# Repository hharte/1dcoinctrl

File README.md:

# 1dcoinctrl - Issue 4

## Western Electric 1D/2D Payphone Controller Interface for Asterisk

# WARNING - This project involves potentially lethal High-Voltage!

**_The coin relay in most payphones operates using +/- 130VDC.  This project uses a DC-DC converter to boost 12VDC to 130VDC.  Construction and operation of this circuit should only be performed by people familiar with best practices when operating with high voltage, and using extreme caution._**

I WILL NOT BE HELD LIABLE FOR INJURY OR DEATH RESULTING FROM BUILDING OR USING THIS CIRCUIT.   BUILD AND USE THIS CIRCUIT AT YOUR OWN RISK.

THIS HARDWARE AND SOFTWARE IS PROVIDED "AS IS", WITHOUT WARRANTY OF ANY KIND, EXPRESS OR IMPLIED, INCLUDING BUT NOT LIMITED TO THE WARRANTIES OF MERCHANTABILITY, FITNESS FOR A PARTICULAR PURPOSE AND NONINFRINGEMENT.  IN NO EVENT SHALL HOWARD M. HARTE BE LIABLE FOR ANY CLAIM, DAMAGES OR OTHER LIABILITY, WHETHER IN AN ACTION OF CONTRACT, TORT OR OTHERWISE, ARISING FROM, OUT OF OR IN CONNECTION WITH THE HARDWARE AND SOFTWARE OR THE USE OR OTHER DEALINGS IN THE HARDWARE AND SOFTWARE. 

# Overview

This project aims to emulate a coin line as required by the older "dumb" (ie, non-COCOT) payphones such as the Western Electric 1D "Fortress" series.  This coin line interface connects in between an Asterisk PBX and the payphone.  It provides the coin control functionality as well as the ability to determine whether an initial rate has been deposited, and can also perform the "stuck coin" test.

This project is based on another open-source project (see References below) and has the following goals:

1. Real coin-line signaling, while preserving the payphone earth ground.  This requires both +130VDC (coin collect) and -130VDC (coin refund) as well as +25VDC for the "stuck coin" test and -25VDC for the "initial rate" test.
2. The ability to provide up to four coin lines in a single unit.
3. The ability to count dial pulses from Rotary payphones and provide the digits out-of-band to Asterisk.
4. The ability to be [red-boxed](http://en.wikipedia.org/wiki/Red_box_(phreaking)).

# Pay phone

The payphone is a standard Western Electric 1D phone with a 32B "dumb" chassis.  I also verified that Western Electric 32A and TeleService 4032C chassis work well with this design.

# Coin Line Signaling

All coin line signaling happens with respect to TIP and Ground with the RING open. For the tests, current flowing when voltage is applied indicates that either a coin is present in the hopper, or the initial rate has been deposited.

<table>
  <tr>
   <td>Voltage
   </td>
   <td>Operation
   </td>
  </tr>
  <tr>
   <td>+130VDC
   </td>
   <td>Collect coins.
   </td>
  </tr>
  <tr>
   <td>-130VDC
   </td>
   <td>Refund coins.
   </td>
  </tr>
  <tr>
   <td>+25VDC
   </td>
   <td>Stuck Coin Test
   </td>
  </tr>
  <tr>
   <td>-25VDC
   </td>
   <td>Initial Rate Test
   </td>
  </tr>
</table>

## Controlling the Coin Line Signaling

Control of the coin lines is handled by a PIC18F47Q84 microcontroller.  This microcontroller can sense the line polarity and ON/OFF hook status, the test status, and can control the relays on the controller.

There are three relays that provide common control, and two additional relays per line.

### Common Control Relays

1. **_REFUND_** Relay: When operated will prepare negative voltage to be applied to the TIP when the selected line's COIN_CONTROL relay is operated.  When this relay is operated, either Coin Refund or Initial Rate Test will be performed based on the state of the DISPOSITION relay.

2. **_DISPOSITION_** Relay: When operated will prepare high voltage (either +130VDC or -130VDC, depending on the state of the REFUND relay) to be applied to the TIP when the selected line's COIN_CONTROL relay is operated.  When the DISPOSITION relay is not operated, low voltage (+25VDC or -25VDC) will be applied in order to perform either the initial rate test or the stuck coin test.

3. **_POLE-CHANGER_** Relay: This relay is used to swap the Vout+ and Vout- on the output of the 130VDC DC-DC converter so that both +130VDC and -130VDC are available depending on whether the coin should be collected or refunded.

### Per-Line Relays, one each per coin line:

1. **_HOLD_** Relay: When operated will shunt the TIP and RING towards the CO (Asterisk PBX in our case) with a 120-ohm resistor.  This will keep the line on hold while coin disposition or rate tests are performed.

2. **_COIN_CONTROL_** Relay: When operated, will apply the coin control voltage to the TIP towards the payphone.  When not operated, the TIP and RING from the CO (Asterisk PBX) will be passed through to the payphone.

### Sensors

There are several opto-isolated sensors in the design to provide status to the microcontroller.

1. **_TEST_STATUS_** sensor will go low when current is flowing during a test.  It will be high when current is not flowing.

2. Per-line **_OFF_HOOK_F and OFF_HOOK_R_** sensors (one per line) will go low when current is flowing through the loop to the CO (Asterisk PBX) and can detect forward and reverse polarity.  This current will be flowing either when the payphone is off-hook or when the line is on hold.  Polarity reversal answer supervision, if provided by your telephone line, can be used to determine whether coins should be collected or refunded.  These LEDs will blink rapidly while a rotary payphone is being dialed.

# Microcontroller Firmware

The microcontroller firmware uses the [Arduino](https://www.arduino.cc/) development environment with the [DxCore library](https://github.com/SpenceKonde/DxCore) for ease of development.  The firmware provides a command-line interface via the serial port that uses a command set modeled after the familiar Hayes AT command set.

The command syntax is AT followed by a single character command, and an optional number [1-4] for the coin line to operate on.  If the coin line is omitted, the previously used coin line is assumed.

Commands are as follows:

<table>
  <tr>
   <td><strong><em>Command</em></strong>
   </td>
   <td><strong><em>Description</em></strong>
   </td>
   <td><strong><em>Response</em></strong>
   </td>
  </tr>
  <tr>
   <td>AT
   </td>
   <td>Attention
   </td>
   <td>OK
   </td>
  </tr>
  <tr>
   <td>ATZ
   </td>
   <td>Reset
   </td>
   <td>OK
   </td>
  </tr>
  <tr>
   <td>ATC
   </td>
   <td>Collect coin
   </td>
   <td>OK
   </td>
  </tr>
  <tr>
   <td>ATR
   </td>
   <td>Refund coin
   </td>
   <td>OK
   </td>
  </tr>
  <tr>
   <td>ATI
   </td>
   <td>Initial rate test
   </td>
   <td>0 = Initial rate not deposited
<p>
1 = Initial rate deposited
   </td>
  </tr>
  <tr>
   <td>ATS
   </td>
   <td>Stuck coin test
   </td>
   <td>0 = No coin in escrow.
<p>
1 = Coin in escrow.
   </td>
  </tr>
  <tr>
   <td>ATQ
   </td>
   <td>Query hook state
   </td>
   <td>0 = On hook
<p>
1 = Off hook (normal polarity)
<p>
2 = Off hook (reversed polarity)
   </td>
  </tr>
  <tr>
   <td>ATL
   </td>
   <td>Query selected coin line
   </td>
   <td>1-4
   </td>
  </tr>
  <tr>
   <td>ATH
   </td>
   <td>Hold CO line
   </td>
   <td>OK
   </td>
  </tr>
  <tr>
   <td>ATU
   </td>
   <td>Un-hold CO line
   </td>
   <td>OK
   </td>
  </tr>
  <tr>
   <td>ATD
   </td>
   <td>Dump current controller state
   </td>
   <td>OK
   </td>
  </tr>
  <tr>
   <td>ATE
   </td>
   <td>Stress test 100 refunds (1s apart)
   </td>
   <td>OK
   </td>
  </tr>
  <tr>
   <td>ATT
   </td>
   <td>Coin line simulation
   </td>
   <td>Need hard reset to exit.
   </td>
  </tr>
  <tr>
   <td>ATV
   </td>
   <td>Display firmware version
   </td>
   <td>OK
   </td>
  </tr>
  <tr>
   <td>AT?
   </td>
   <td>Help
   </td>
   <td>Display command help
   </td>
  </tr>
</table>

# Building the Hardware

## Components

The components for this board can be ordered from Digi-Key using [this parts list](https://www.digikey.com/en/mylists/list/BGQKKBOZGS).  The list includes all components and accessories to build the full board supporting all four coin lines.  The user will need to provide their own 12VDC power supply.

There is an [interactive Bill of Materials here](https://html-preview.github.io/?url=https://github.com/hharte/1dcoinctrl/blob/main/hardware/bom/ibom.html).

## Stuffing Options

### Relay Coil Voltage and DC-DC Converters

The schematic/BOM supports either 5V or 12V coil relays.  Alternatively, the board may be built to support a 24VDC input voltage and the user may use 24V coil relays.  In this case, PS1 and PS2 need to change:

<table>
  <tr>
   <td>Power Supply Voltage
   </td>
   <td>Relay Coil Voltage
   </td>
   <td>J8 Setting
   </td>
   <td>PS1 Part
   </td>
   <td>PS2 Part
   </td>
  </tr>
  <tr>
   <td>+12VDC*
   </td>
   <td>12V*
   </td>
   <td>1-2
   </td>
   <td>R12-100B
   </td>
   <td>IA1224S
   </td>
  </tr>
  <tr>
   <td>+12VDC
   </td>
   <td>5V
   </td>
   <td>2-3
   </td>
   <td>R12-100B
   </td>
   <td>IA1224S
   </td>
  </tr>
  <tr>
   <td>+24VDC
   </td>
   <td>5V
   </td>
   <td>2-3
   </td>
   <td>R24-100B
   </td>
   <td>IA2424S
   </td>
  </tr>
  <tr>
   <td>+24VDC
   </td>
   <td>24V
   </td>
   <td>1-2
   </td>
   <td>R24-100B
   </td>
   <td>IA2424S
   </td>
  </tr>
</table>

### Serial Port - RS-232 or 5V TTL-level UART

Communication with the host computer is either via RS-232 or 5V TTL-level UART.

<table>
  <tr>
   <td><strong><em>Reference Designator</em></strong>
   </td>
   <td><strong><em>RS-232</em></strong>
   </td>
   <td><strong><em>TTL UART </em></strong>
   </td>
   <td><strong><em>Notes</em></strong>
   </td>
  </tr>
  <tr>
   <td>U2
   </td>
   <td>✔
   </td>
   <td>
   </td>
   <td>MAX202 or equivalent.
   </td>
  </tr>
  <tr>
   <td>C3,C4,C5,C6,C8
   </td>
   <td>✔
   </td>
   <td>
   </td>
   <td>0.1uF Capacitor
   </td>
  </tr>
  <tr>
   <td>R2
   </td>
   <td>✔
   </td>
   <td>
   </td>
   <td>
   </td>
  </tr>
  <tr>
   <td>C7
   </td>
   <td>✔
   </td>
   <td>
   </td>
   <td>4700pF Capacitor
   </td>
  </tr>
  <tr>
   <td>JP1
   </td>
   <td>✔
   </td>
   <td>
   </td>
   <td>Programming Enable (to program Microcontroller)
<p>
Remove jumper from JP1 when using a standard FTDI 5V TTL UART cable.
   </td>
  </tr>
  <tr>
   <td>JP2, JP3
   </td>
   <td>1-2
   </td>
   <td>2-3
   </td>
   <td>Jumper 1-2 for RS-232 or 2-3 for TTL UART.
   </td>
  </tr>
  <tr>
   <td>J5
   </td>
   <td>✔
   </td>
   <td>✔
   </td>
   <td>6-pin right angle 0.1” male header.
   </td>
  </tr>
</table>

Note: To switch between RS-232 and TTL UART, U2 can be removed from the socket, and the 5V TTL UART cable attached to J5.  When switching back to the RS-232 port, detach the 5V TTL UART cable from J5 and reinstall U2.  In addition to the TTL UART, J5 is also used to program the microcontroller.

### External +/-130VDC Coin Collect / Refund Supply

The board can accommodate an external +/-130VDC supply with the following assembly changes:

<table>
  <tr>
   <td><strong><em>Reference Designator</em></strong>
   </td>
   <td><strong><em>Populate</em></strong>
   </td>
   <td><strong><em>Do Not Populate</em></strong>
   </td>
   <td><strong><em>Notes</em></strong>
   </td>
  </tr>
  <tr>
   <td>PS1
   </td>
   <td>
   </td>
   <td>✔
   </td>
   <td>
   </td>
  </tr>
  <tr>
   <td>C18
   </td>
   <td>
   </td>
   <td>✔
   </td>
   <td>
   </td>
  </tr>
  <tr>
   <td>D2
   </td>
   <td>
   </td>
   <td>✔
   </td>
   <td>
   </td>
  </tr>
  <tr>
   <td>D1
   </td>
   <td>
   </td>
   <td>✔
   </td>
   <td>V_COIN_RELAY (130VDC) Indicator LED.
   </td>
  </tr>
  <tr>
   <td>K1
   </td>
   <td>
   </td>
   <td>✔
   </td>
   <td>Pole Changer Relay
   </td>
  </tr>
  <tr>
   <td>R15
   </td>
   <td>
   </td>
   <td>✔
   </td>
   <td>
   </td>
  </tr>
  <tr>
   <td>R5
   </td>
   <td>
   </td>
   <td>✔
   </td>
   <td>5K Potentiometer
   </td>
  </tr>
  <tr>
   <td>R9
   </td>
   <td>
   </td>
   <td>✔
   </td>
   <td>V_COIN_RELAY (130VDC) Indicator LED current limit.
   </td>
  </tr>
  <tr>
   <td>F2, F3
   </td>
   <td>✔
   </td>
   <td>
   </td>
   <td>125mA Fuse
   </td>
  </tr>
  <tr>
   <td>R10, R11
   </td>
   <td>✔
   </td>
   <td>
   </td>
   <td>+/- 130VDC LED current limiting.
   </td>
  </tr>
  <tr>
   <td>D3, D13
   </td>
   <td>✔
   </td>
   <td>
   </td>
   <td>+/- 130VDC Indicator LEDs
   </td>
  </tr>
</table>

**_Note:_** To switch between external +/-130 VDC supply and the on-board DC-DC converter:

* At minimum, PS1 and K1 should be removed when using the external supply.  If desired, a socket can be made for PS1 by removing several pins from a 24-pin 0.6” wide, machined-pin DIP socket.  A socket can be made for K1 in a similar fashion, using a 16-pin machined-pin DIP socket.
* At minimum, F2, F3 should be removed when using the on-board DC-DC converter.  This is essential for two reasons:
1. Safety: Prevent V_COIN_RELAY (130VDC) from being present on the +/-130VDC terminals of J1.
2. Protection: to ensure that V_COIN_RELAY is not shorted to the +/-130VDC supply during operation.

**_Warning_**

D1, when illuminated, indicates that 130VDC is present on the board.  While this LED is lit, be very careful not to touch the high-voltage section of the board.

D3, D13, when illuminated, indicates that external +/-130VDC is present on the board.  While either of these LEDs are lit, be very careful not to touch the high-voltage section of the board.

### Less Than Four Coin Lines

The controller can be assembled to support fewer than four pay phones.  If only one pay phone is desired, U3 (7406) can be omitted, as well as components associated with lines 2 through 4.

<table>
  <tr>
   <td><strong><em>Coin Line</em></strong>
   </td>
   <td><strong><em>Reference Designator</em></strong>
   </td>
   <td><strong><em>Do Not Populate</em></strong>
   </td>
   <td><strong><em>Notes</em></strong>
   </td>
  </tr>
  <tr>
   <td rowspan="5" >2
   </td>
   <td>D19
   </td>
   <td>✔
   </td>
   <td>Bi-Color LED
   </td>
  </tr>
  <tr>
   <td>D5, D7
   </td>
   <td>✔
   </td>
   <td>1N4148 Switching Diodes
   </td>
  </tr>
  <tr>
   <td>R4, R16, R24
   </td>
   <td>✔
   </td>
   <td>
   </td>
  </tr>
  <tr>
   <td>K3, K6
   </td>
   <td>✔
   </td>
   <td>Hold / Coin Control Relays
   </td>
  </tr>
  <tr>
   <td>U5
   </td>
   <td>✔
   </td>
   <td>Optoisolator
   </td>
  </tr>
  <tr>
   <td rowspan="5" >3
   </td>
   <td>D20
   </td>
   <td>✔
   </td>
   <td>Bi-Color LED
   </td>
  </tr>
  <tr>
   <td>D8, D10
   </td>
   <td>✔
   </td>
   <td>1N4148 Switching Diodes
   </td>
  </tr>
  <tr>
   <td>R3, R18, R26
   </td>
   <td>✔
   </td>
   <td>
   </td>
  </tr>
  <tr>
   <td>K5, K7
   </td>
   <td>✔
   </td>
   <td>Hold / Coin Control Relays
   </td>
  </tr>
  <tr>
   <td>U4
   </td>
   <td>✔
   </td>
   <td>Optoisolator
   </td>
  </tr>
  <tr>
   <td rowspan="5" >4
   </td>
   <td>D21
   </td>
   <td>✔
   </td>
   <td>Bi-Color LED
   </td>
  </tr>
  <tr>
   <td>D9, D11
   </td>
   <td>✔
   </td>
   <td>1N4148 Switching Diodes
   </td>
  </tr>
  <tr>
   <td>R1, R19, R25
   </td>
   <td>✔
   </td>
   <td>
   </td>
  </tr>
  <tr>
   <td>K8, K9
   </td>
   <td>✔
   </td>
   <td>Hold / Coin Control Relays
   </td>
  </tr>
  <tr>
   <td>U1
   </td>
   <td>✔
   </td>
   <td>Optoisolator
   </td>
  </tr>
</table>

## Enclosure

Included in the parts list is a [Hammond 160mm extruded aluminum enclosure](https://www.hammfg.com/files/parts/pdf/1455R1602BK.pdf).  This enclosure includes end caps that can be cut/drilled for the LEDs in the front of the board, as well as the connectors in the rear.  Alternatively, a design for 3D-printed end caps is included in this project.

## Issue 4 PCB

### Microcontroller Replacement

The PIC microcontroller in previous revisions was replaced with an [AVR128DA28](https://www.microchip.com/en-us/product/avr128da28) in the DIP-28 package.  The firmware uses the [Arduino](https://www.arduino.cc/) development environment with the [DxCore library](https://github.com/SpenceKonde/DxCore) for ease of development and programming.

### Other changes between Issue 3 and Issue 4:

* Additional LED connected to microcontroller pin PA7 under firmware control.

Still need to validate:

1. Coin Lines 2, 3, 4.
2. FTDI 5V TTL UART Connection.
3. 

# Connections

## J3, J4 - Lines

The controller supports four CO lines and four coin collectors via two RJ45 connectors.  Each of these connectors is wired according to [T568A](https://en.wikipedia.org/wiki/ANSI/TIA-568).

<table>
  <tr>
   <td><strong><em>Pin</em></strong>
   </td>
   <td><strong><em>T568A Pair</em></strong>
   </td>
   <td><strong><em>J4</em></strong>
<p>
<strong><em>CO Lines</em></strong>
   </td>
   <td><strong><em>J3</em></strong>
<p>
<strong><em>Coin Phones</em></strong>
   </td>
   <td><strong><em>Color</em></strong>
   </td>
  </tr>
  <tr>
   <td>1
   </td>
   <td>3
   </td>
   <td>L3 Tip
   </td>
   <td>L3 Tip
   </td>
   <td>White/Green
   </td>
  </tr>
  <tr>
   <td>2
   </td>
   <td>3
   </td>
   <td>L3 Ring
   </td>
   <td>L3 Ring
   </td>
   <td>Green/White
   </td>
  </tr>
  <tr>
   <td>3
   </td>
   <td>2
   </td>
   <td>L2 Tip
   </td>
   <td>L2 Tip
   </td>
   <td>White/Orange
   </td>
  </tr>
  <tr>
   <td>4
   </td>
   <td>1
   </td>
   <td>L1 Ring
   </td>
   <td>L1 Ring
   </td>
   <td>Blue/White
   </td>
  </tr>
  <tr>
   <td>5
   </td>
   <td>1
   </td>
   <td>L1 Tip
   </td>
   <td>L1 Tip
   </td>
   <td>White/Blue
   </td>
  </tr>
  <tr>
   <td>6
   </td>
   <td>2
   </td>
   <td>L2 Ring
   </td>
   <td>L2 Ring
   </td>
   <td>Orange/White
   </td>
  </tr>
  <tr>
   <td>7
   </td>
   <td>4
   </td>
   <td>L4 Tip
   </td>
   <td>L4 Tip
   </td>
   <td>White/Brown
   </td>
  </tr>
  <tr>
   <td>8
   </td>
   <td>4
   </td>
   <td>L4 Ring
   </td>
   <td>L4 Ring
   </td>
   <td>Brown/White
   </td>
  </tr>
</table>

## J1 - Power

<table>
  <tr>
   <td>Pin
   </td>
   <td>Description
   </td>
  </tr>
  <tr>
   <td>+12VDC
   </td>
   <td>Positive 12V Input.  This must be positive with respect to GROUND.
   </td>
  </tr>
  <tr>
   <td>GROUND
   </td>
   <td>Power Supply Ground (Must be the same as earth ground.)
   </td>
  </tr>
  <tr>
   <td>+130VDC_IN
   </td>
   <td>Coin voltage + (Optional, board assembly option.)
   </td>
  </tr>
  <tr>
   <td>-130VDC_IN
   </td>
   <td>Coin voltage - (Optional, board assembly option.)
   </td>
  </tr>
</table>

## Earth Ground Lug

Coin control and tests are with respect to earth ground.  All payphones must be grounded and bonded for safety as well as to provide a return path for coin collect/refund as well as the initial rate and stuck coin tests.  If the payphone and coin line controller are not grounded, they will not work properly.

## Serial Port

Communication with the host computer running Asterisk is via an RS-232 serial port at J6.  If the user does not wish to use RS-232 levels to communicate with the computer, then the MAX202 IC at U2 should be removed from the socket.  With the MAX202 removed, a [USB to 5V TTL Serial cable](https://www.digikey.com/en/products/detail/ftdi-future-technology-devices-international-ltd/TTL-232R-5V/2003493) connected to J5 (Ground pin on the left when looking at the rear of the controller) can be used to connect the coin controller to a PC via USB.

# Indicators

The controller includes several indicator LEDs.  Most are on the front panel; however, high-voltage warning LEDs are present inside the enclosure.

<table>
  <tr>
   <td><strong><em>Reference Designator</em></strong>
   </td>
   <td><strong><em>Indicates</em></strong>
   </td>
   <td><strong><em>Notes</em></strong>
   </td>
  </tr>
  <tr>
   <td>D15
   </td>
   <td>Power
   </td>
   <td>Illuminates when +5VDC is present, indicating that the coin controller board is powered.
   </td>
  </tr>
  <tr>
   <td>D16
   </td>
   <td>MCU Status
   </td>
   <td>Illuminated under firmware (PA7) control by the on-board microcontroller.
   </td>
  </tr>
  <tr>
   <td>D17
   </td>
   <td>Test Status
   </td>
   <td>Illuminates during the stuck coin test or the initial rate test if the test result is positive: coin is stuck, initial rate is deposited.  This status is input to the microcontroller on PA6.
   </td>
  </tr>
  <tr>
   <td>D18
   </td>
   <td>L1 Status
   </td>
   <td>Line 1 Hook State:
<ul>

<li>Not illuminated: On-hook

<li>Green: Normal Polarity

<li>Red: Reverse Polarity (Answer supervision.)
</li>
</ul>
   </td>
  </tr>
  <tr>
   <td>D19
   </td>
   <td>L2 Status
   </td>
   <td>Line 2 Hook State
   </td>
  </tr>
  <tr>
   <td>D20
   </td>
   <td>L3 Status
   </td>
   <td>Line 1 Hook State
   </td>
  </tr>
  <tr>
   <td>D21
   </td>
   <td>L4 Status
   </td>
   <td>Line 1 Hook State
   </td>
  </tr>
  <tr>
   <td>D1
   </td>
   <td>V_COIN_RELAY
   </td>
   <td>(Internal) 130VDC produced by the on-board DC-DC converter.
   </td>
  </tr>
  <tr>
   <td>D3
   </td>
   <td>+130VDC
   </td>
   <td>(Internal) Indicates +130VDC from the external supply is present.
   </td>
  </tr>
  <tr>
   <td>D13
   </td>
   <td>-130VDC
   </td>
   <td>(Internal) Indicates -130VDC from the external supply is present.
   </td>
  </tr>
</table>

# Asterisk PBX Modifications

Modifications to Asterisk in order to recognize the 1700/2200Hz coin tones is based on [Joshua Stein's project](https://github.com/jcs/payphone) although I modified them to treat the 1700/2200Hz tones as a 5th row/column in the standard [DTMF](http://en.wikipedia.org/wiki/Dual-tone_multi-frequency_signaling) decoding routine in Asterisk's main/dsp.c.

The Asterisk AGI script is not complete, but at present it will prompt for money and can recognize the coin tones.  It will complete the call after 25 cents has been deposited.

## References

* [https://github.com/jcs/payphone](https://github.com/jcs/payphone)
* [Bell System Public Services Crafts' Manual for Station, Network, and Testboard](http://wedophones.com/TheBellSystem/pdf/bsp/coin/PublicServices1.pdf)

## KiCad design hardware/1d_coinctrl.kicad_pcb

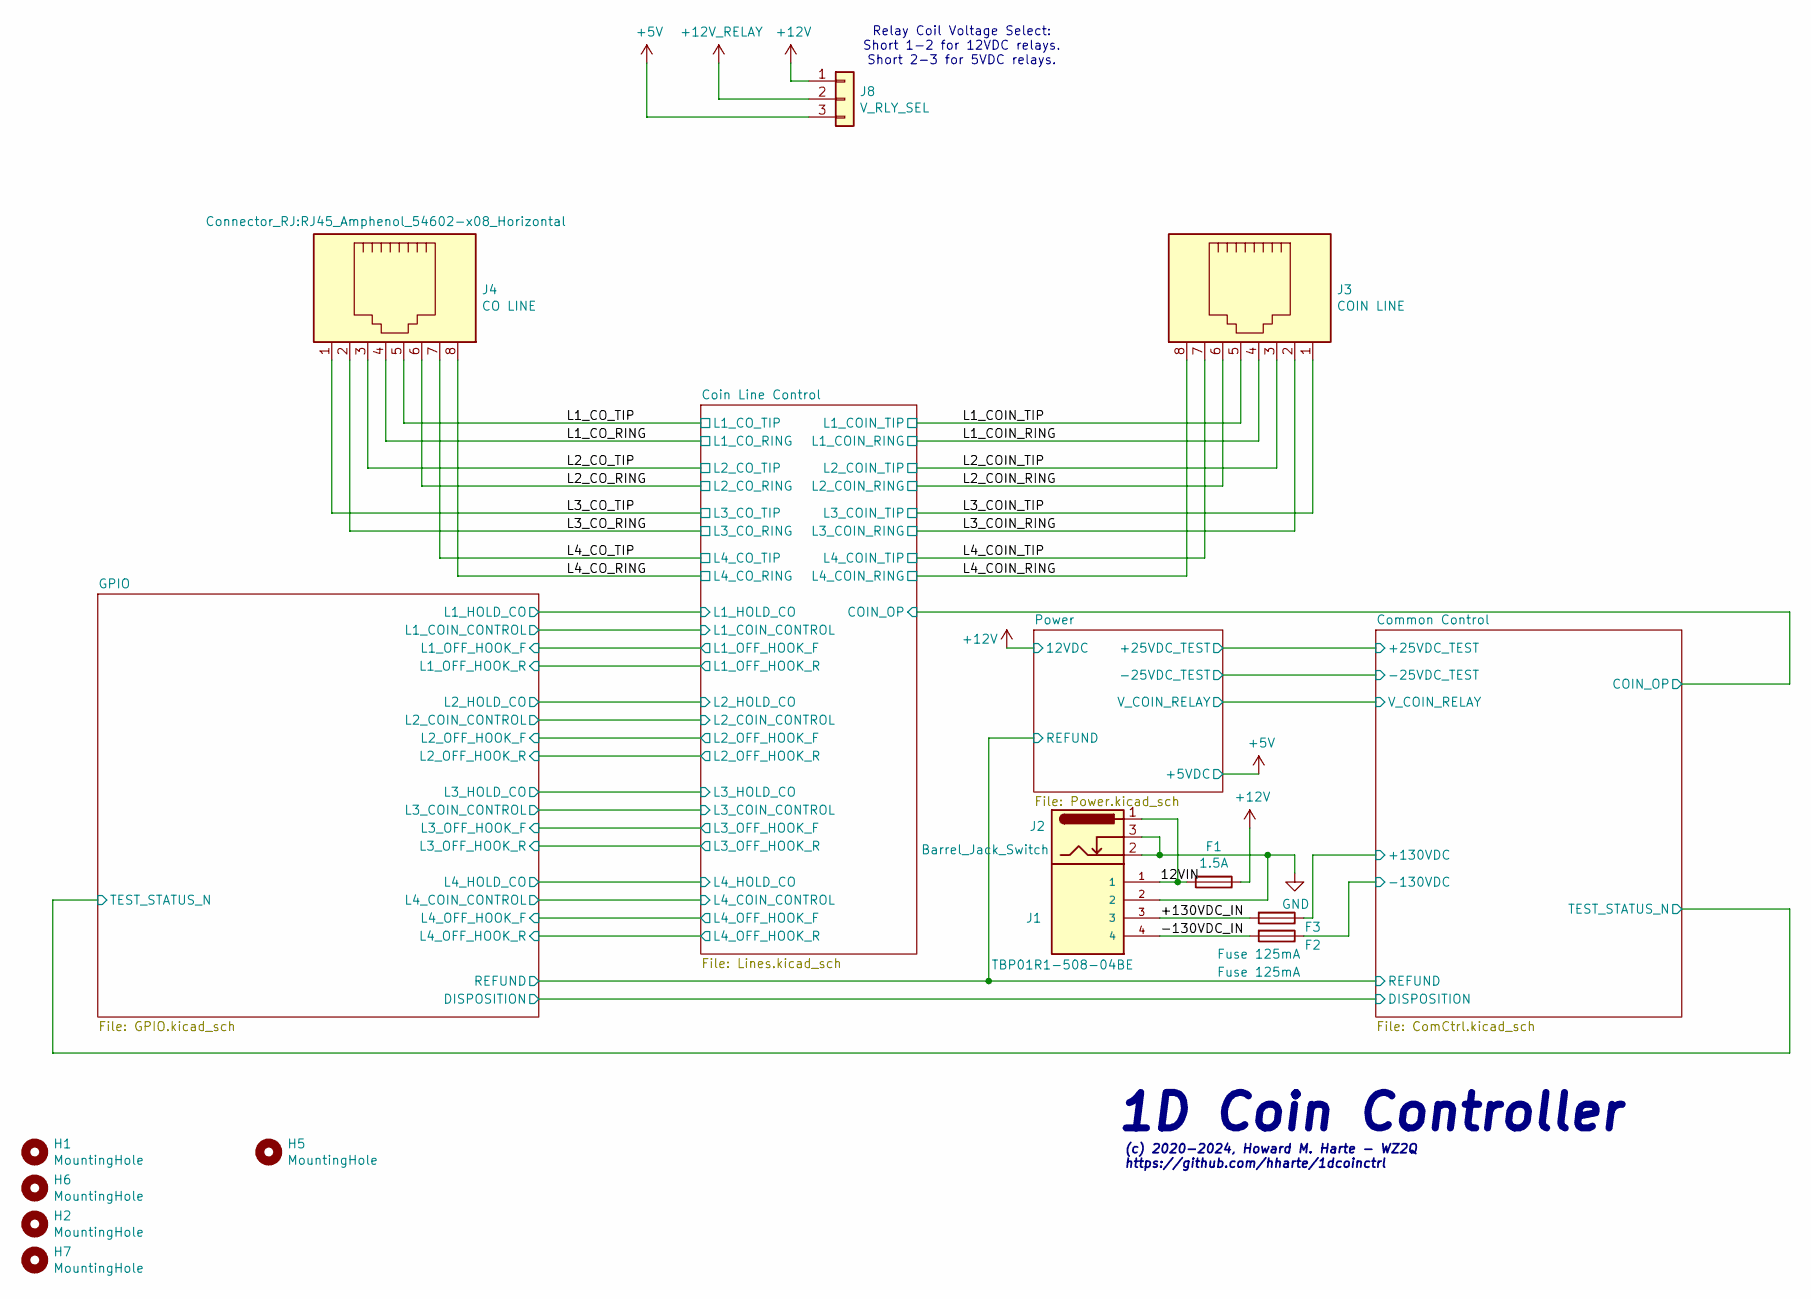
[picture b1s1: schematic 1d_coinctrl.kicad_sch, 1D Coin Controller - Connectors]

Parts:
F1: 1.5A; R_Axial_DIN0207_L6.3mm_D2.5mm_P10.16mm_Horizontal; MPN 025101.5MXL; Digi-Key_PN F2319-ND
F2, F3: Fuse 125mA; R_Axial_DIN0207_L6.3mm_D2.5mm_P10.16mm_Horizontal; MPN 0251.125NAT1L; Digi-Key_PN F10763CT-ND
H1, H2, H5, H6, H7: MountingHole; MountingHole_3.7mm_Pad
J1: TBP01R1-508-04BE; CUI_TBP01R1-508-04BE; MPN TBP01R1-508-04BE; Digi-Key_PN 102-6408-ND
J2: Barrel_Jack_Switch; BarrelJack_Horizontal; MPN RAPC722BK
J3: COIN LINE; RJ45_Amphenol_54602-x08_Horizontal; MPN 54602-908LF; Digi-Key_PN 609-1046-ND
J4: CO LINE; RJ45_Amphenol_54602-x08_Horizontal; MPN 54602-908LF; Digi-Key_PN 609-1046-ND
J8: V_RLY_SEL; PinHeader_1x03_P2.54mm_Vertical

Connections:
+5V: J8.3; also elsewhere on the board
+12V: F1.1, J8.1; also elsewhere on the board
+12V_RELAY: J8.2; also elsewhere on the board
/12VIN: F1.2, J1.1, J2.1
/+130VDC_IN: F3.2, J1.3
/-130VDC_IN: F2.2, J1.4
/Common Control/+130VDC: F3.1; also elsewhere on the board
/Common Control/-130VDC: F2.1; also elsewhere on the board
/L1_COIN_RING: J3.4; also elsewhere on the board
/L1_COIN_TIP: J3.5; also elsewhere on the board
/L1_CO_RING: J4.4; also elsewhere on the board
/L1_CO_TIP: J4.5; also elsewhere on the board
/L2_COIN_RING: J3.6; also elsewhere on the board
/L2_COIN_TIP: J3.3; also elsewhere on the board
/L2_CO_RING: J4.6; also elsewhere on the board
/L2_CO_TIP: J4.3; also elsewhere on the board
/L3_COIN_RING: J3.2; also elsewhere on the board
/L3_COIN_TIP: J3.1; also elsewhere on the board
/L3_CO_RING: J4.2; also elsewhere on the board
/L3_CO_TIP: J4.1; also elsewhere on the board
/L4_COIN_RING: J3.8; also elsewhere on the board
/L4_COIN_TIP: J3.7; also elsewhere on the board
/L4_CO_RING: J4.8; also elsewhere on the board
/L4_CO_TIP: J4.7; also elsewhere on the board
GND: J1.2, J2.2, J2.3; also elsewhere on the board

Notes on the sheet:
(c) 2020-2024, Howard M. Harte - WZ2Q https://github.com/hharte/1dcoinctrl
Relay Coil Voltage Select: Short 1-2 for 12VDC relays. Short 2-3 for 5VDC relays.
1D Coin Controller

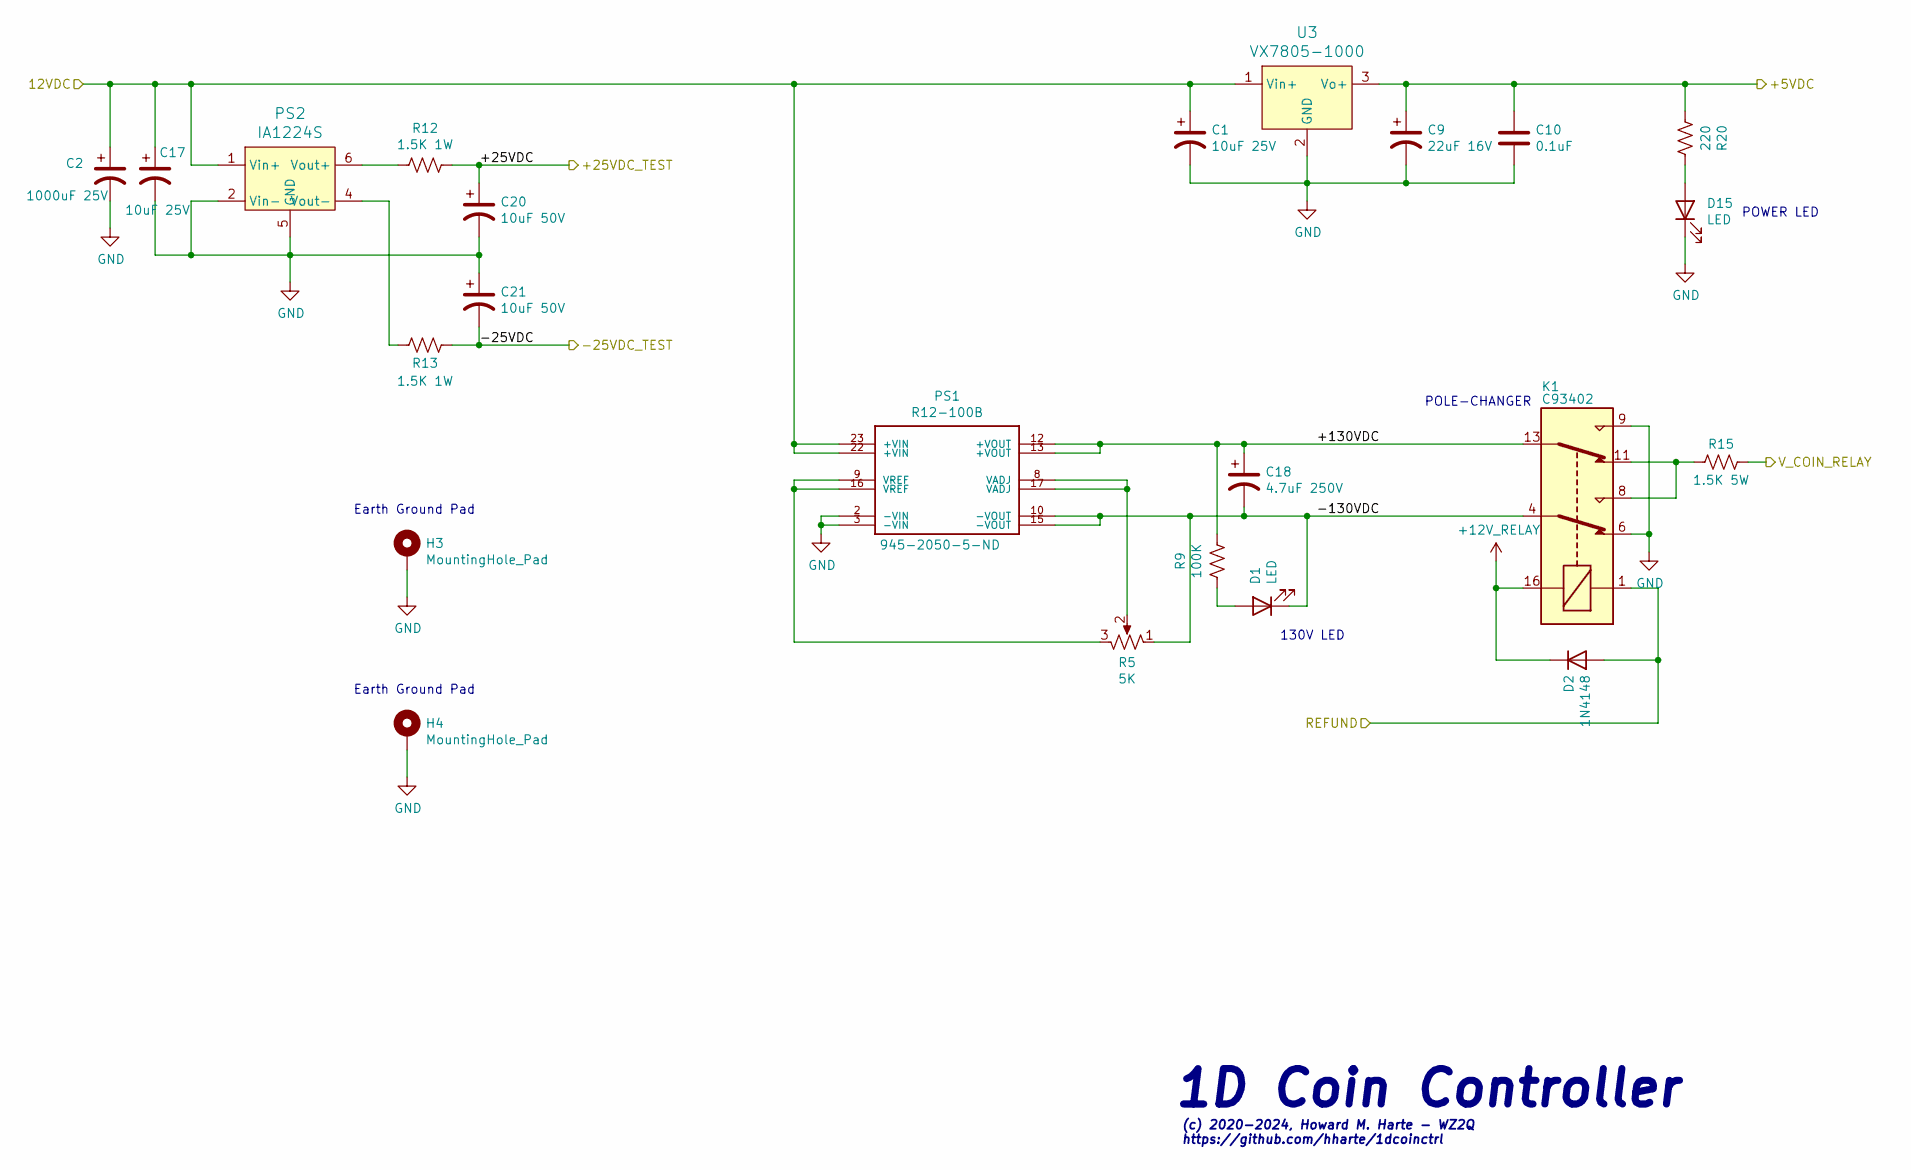
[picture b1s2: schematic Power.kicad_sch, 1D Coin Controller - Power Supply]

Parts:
C1, C17: 10uF 25V; C_Disc_D6.0mm_W4.4mm_P5.00mm; MPN FA26X7R1E106KRU06; Digi-Key_PN 445-180683-1-ND
C2: 1000uF 25V; CP_Radial_D12.5mm_P5.00mm; MPN ECA-1HHG102; Digi-Key_PN P5575-ND
C9: 22uF 16V; C_Disc_D6.0mm_W4.4mm_P5.00mm; MPN FK20X7R1C226MR000; Digi-Key_PN 445-FK20X7R1C226MR000-ND
C10: 0.1uF; C_Disc_D3.0mm_W2.0mm_P2.50mm; MPN K104M15X7RF5TL2; Digi-Key_PN 56-K104M15X7RF5TL2CT-ND
C18: 4.7uF 250V; CP_Radial_D8.0mm_P3.50mm; MPN SEK4R7M250ST; Digi-Key_PN 338-2361-ND
C20, C21: 10uF 50V; CP_Radial_D6.3mm_P2.50mm; MPN ECA-1JM100I; Digi-Key_PN P19534CT-ND
D1, D15: LED; LED_D5.0mm; MPN XLUR12D; Digi-Key_PN 1497-1031-ND
D2: 1N4148; D_DO-35_SOD27_P7.62mm_Horizontal; MPN 1N4148TA; Digi-Key_PN 1N4148TACT-ND
H3, H4: MountingHole_Pad; MountingHole_3.7mm_Pad
K1: C93402; Relay_DPDT_Omron_G5V-2; MPN C93402; Digi-Key_PN PB1125-ND
PS1: R12-100B; CONV_R12-100B; MPN R12-100B; Digi-Key_PN 945-2050-5-ND
PS2: IA1224S; MPN IA1224S; Digi-Key_PN 1470-1364-5-ND
R5: 5K; Potentiometer_Bourns_3266W_Vertical; MPN 64WR5KLF; Digi-Key_PN 987-1067-ND
R9: 100K; R_Axial_DIN0207_L6.3mm_D2.5mm_P7.62mm_Horizontal; MPN CFM12JT100K; Digi-Key_PN S100KHCT-ND
R12, R13: 1.5K 1W; R_Axial_DIN0207_L6.3mm_D2.5mm_P10.16mm_Horizontal; MPN PR01000101501JR500; Digi-Key_PN PPC1.5KW-1CT-ND
R15: 1.5K 5W; R_Axial_Power_L25.0mm_W9.0mm_P30.48mm; MPN EP5WS1K5J; Digi-Key_PN A131371CT-ND
R20: 220; R_Axial_DIN0207_L6.3mm_D2.5mm_P7.62mm_Horizontal; MPN CFM12JT220R; Digi-Key_PN S220HCT-ND
U3: VX7805-1000; MPN VX7805-1000; Digi-Key_PN 102-4253-ND

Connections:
+5V: C9.1, C10.1, R20.2, U3.3 (Vo+); also elsewhere on the board
+12V: C1.1, C2.1, C17.1, PS1.22 (+VIN), PS1.23 (+VIN), PS2.1 (Vin+), U3.1 (Vin+); also elsewhere on the board
+12V_RELAY: D2.1 (K), K1.16; also elsewhere on the board
/Common Control/REFUND: D2.2 (A), K1.1; also elsewhere on the board
/Common Control/V_COIN_RELAY: R15.1; also elsewhere on the board
/Power/+25VDC: C20.1, R12.1; also elsewhere on the board
/Power/+130VDC: C18.1, K1.13, PS1.12 (+VOUT), PS1.13 (+VOUT), R9.1
/Power/-25VDC: C21.2, R13.1; also elsewhere on the board
/Power/-130VDC: C18.2, D1.1 (K), K1.4, PS1.10 (-VOUT), PS1.15 (-VOUT), R5.1
GND: C1.2, C2.2, C9.2, C10.2, C17.2, C20.2, C21.1, D15.1 (K), H3.1, H4.1, K1.6, K1.9, PS1.2 (-VIN), PS1.3 (-VIN), PS2.2 (Vin-), PS2.5 (GND), U3.2 (GND); also elsewhere on the board
unnamed: D1.2 (A), R9.2
unnamed: D15.2 (A), R20.1
unnamed: K1.8, K1.11, R15.2
unnamed: PS1.8 (VADJ), PS1.17 (VADJ), R5.2
unnamed: PS1.9 (VREF), PS1.16 (VREF), R5.3
unnamed: PS2.6 (Vout+), R12.2
unnamed: PS2.4 (Vout-), R13.2

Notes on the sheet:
(c) 2020-2024, Howard M. Harte - WZ2Q https://github.com/hharte/1dcoinctrl
POLE-CHANGER
Earth Ground Pad
1D Coin Controller
130V LED
POWER LED

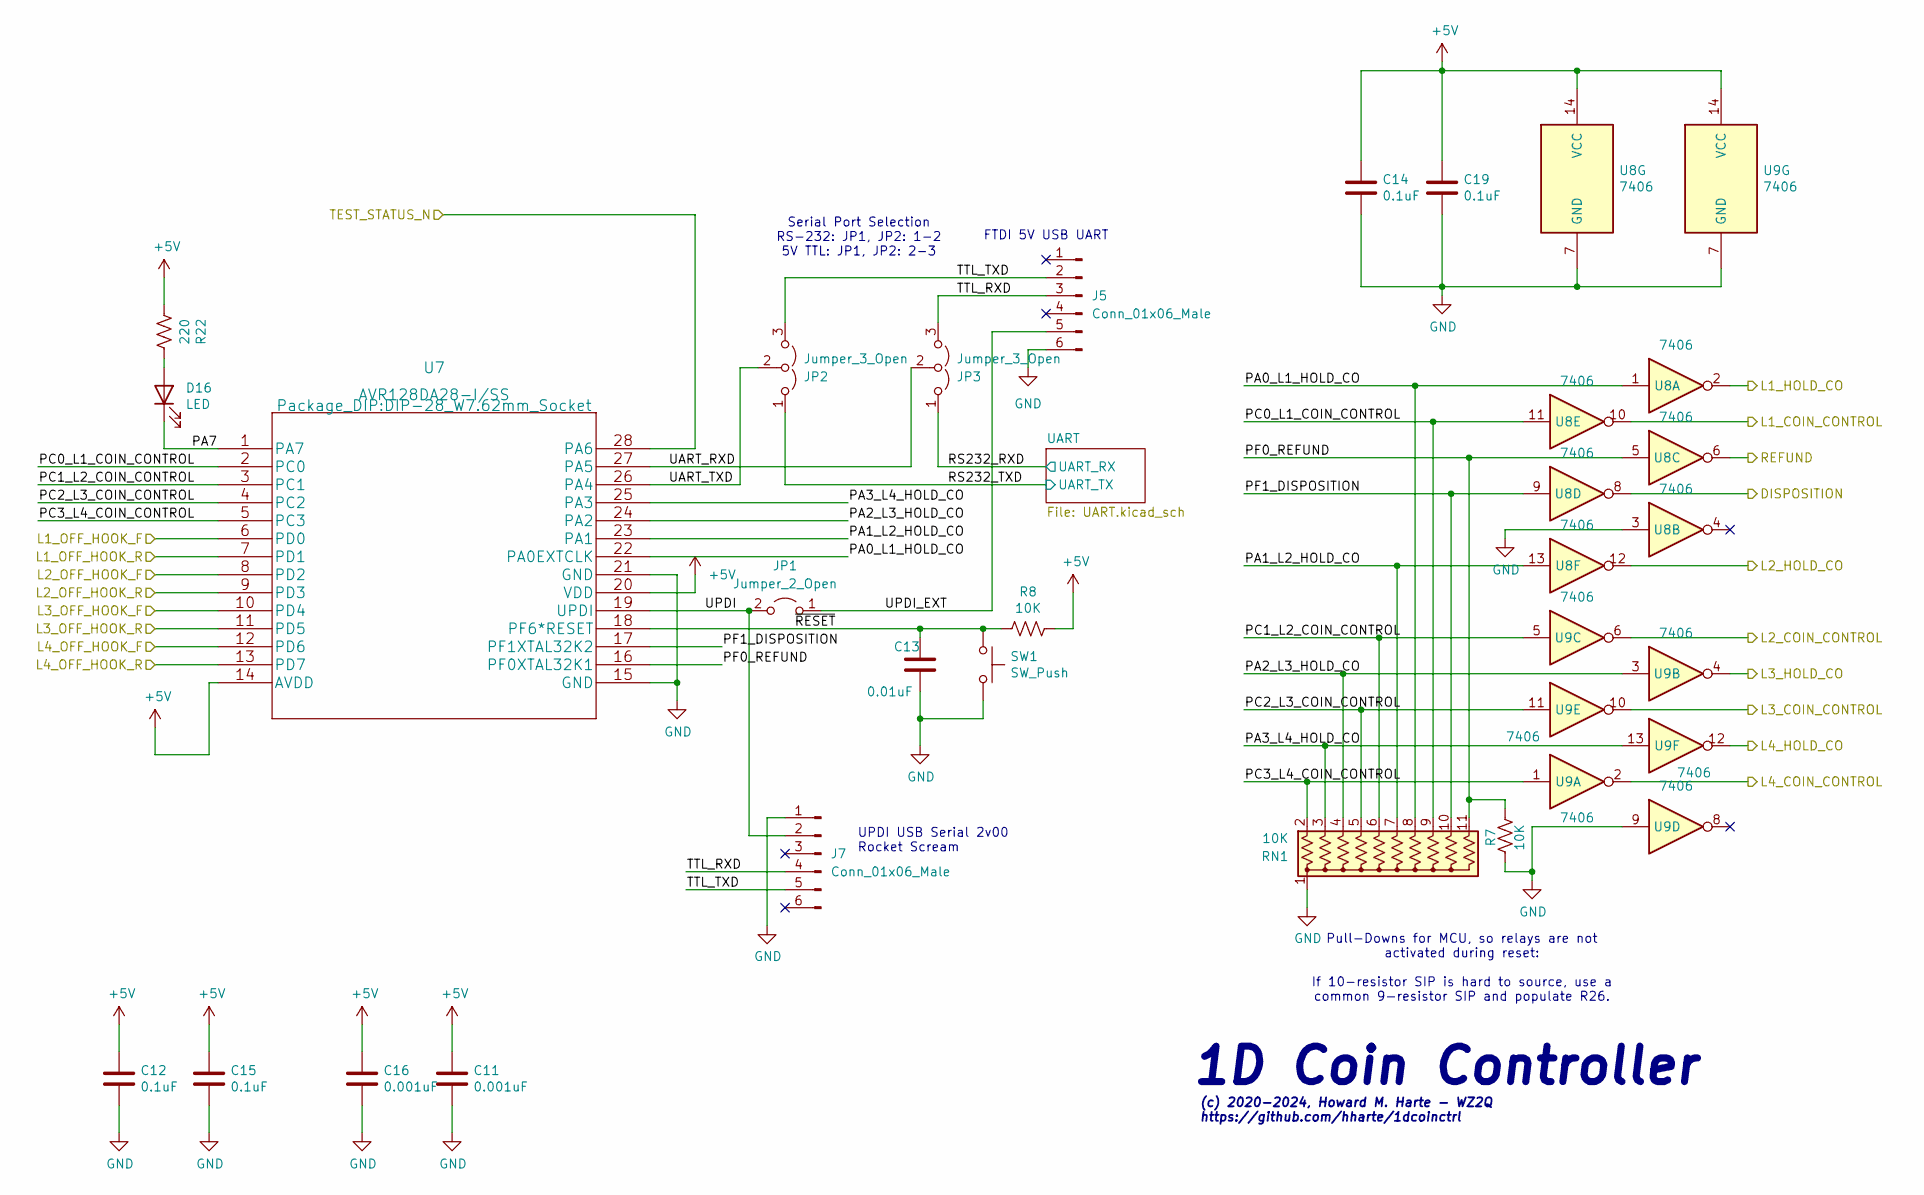
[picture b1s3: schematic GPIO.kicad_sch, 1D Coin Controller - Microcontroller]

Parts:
C11, C16: 0.001uF; C_Disc_D3.0mm_W2.0mm_P2.50mm; MPN K102M15X7RF5UL2; Digi-Key_PN 56-K102M15X7RF5UL2CT-ND
C12, C14, C15, C19: 0.1uF; C_Disc_D3.0mm_W2.0mm_P2.50mm; MPN K104M15X7RF5TL2; Digi-Key_PN 56-K104M15X7RF5TL2CT-ND
C13: 0.01uF; C_Disc_D3.0mm_W1.6mm_P2.50mm; MPN K103K15X7RF5UL2; Digi-Key_PN BC5227CT-ND
D16: LED; LED_D5.0mm; MPN XLUR12D; Digi-Key_PN 1497-1031-ND
J5: Conn_01x06_Male; PinHeader_1x06_P2.54mm_Horizontal; MPN 61300611021; Digi-Key_PN 732-5339-ND
J7: Conn_01x06_Male; PinHeader_1x06_P2.54mm_Vertical; MPN 61300611121; Digi-Key_PN 732-5319-ND
JP1: Jumper_2_Open; PinHeader_1x02_P2.54mm_Vertical
JP2, JP3: Jumper_3_Open; PinHeader_1x03_P2.54mm_Vertical
R7, R8: 10K; R_Axial_DIN0207_L6.3mm_D2.5mm_P7.62mm_Horizontal; MPN CFM12JT10K0; Digi-Key_PN S10KHCT-ND
R22: 220; R_Axial_DIN0207_L6.3mm_D2.5mm_P7.62mm_Horizontal; MPN CFM12JT220R; Digi-Key_PN S220HCT-ND
RN1: 10K; R_Array_SIP11; MPN 4611X-101-103LF; Digi-Key_PN 4611X-101-103LF-ND
SW1: SW_Push; SW_PUSH_6mm; MPN 1301.9302; Digi-Key_PN 486-3458-ND
U7: AVR128DA28-I/SS; DIP-28_W7.62mm_Socket; MPN AVR128DA28-E/SP; Digi-Key_PN 150-AVR128DA28-E/SP-ND
U8, U9: 7406; DIP-14_W7.62mm; MPN SN7406N; Digi-Key_PN 296-1435-5-ND

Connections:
+5V: C11.1, C12.1, C14.1, C15.1, C16.1, C19.1, R8.1, R22.2, U7.14 (AVDD), U7.20 (VDD), U8.14 (VCC), U9.14 (VCC); also elsewhere on the board
/Coin Line Control/L1_COIN_CONTROL: U8.10; also elsewhere on the board
/Coin Line Control/L1_HOLD_CO: U8.2; also elsewhere on the board
/Coin Line Control/L1_OFF_HOOK_F: U7.6 (PD0); also elsewhere on the board
/Coin Line Control/L1_OFF_HOOK_R: U7.7 (PD1); also elsewhere on the board
/Coin Line Control/L2_COIN_CONTROL: U9.6; also elsewhere on the board
/Coin Line Control/L2_HOLD_CO: U8.12; also elsewhere on the board
/Coin Line Control/L2_OFF_HOOK_F: U7.8 (PD2); also elsewhere on the board
/Coin Line Control/L2_OFF_HOOK_R: U7.9 (PD3); also elsewhere on the board
/Coin Line Control/L3_COIN_CONTROL: U9.10; also elsewhere on the board
/Coin Line Control/L3_HOLD_CO: U9.4; also elsewhere on the board
/Coin Line Control/L3_OFF_HOOK_F: U7.10 (PD4); also elsewhere on the board
/Coin Line Control/L3_OFF_HOOK_R: U7.11 (PD5); also elsewhere on the board
/Coin Line Control/L4_COIN_CONTROL: U9.2; also elsewhere on the board
/Coin Line Control/L4_HOLD_CO: U9.12; also elsewhere on the board
/Coin Line Control/L4_OFF_HOOK_F: U7.12 (PD6); also elsewhere on the board
/Coin Line Control/L4_OFF_HOOK_R: U7.13 (PD7); also elsewhere on the board
/Common Control/DISPOSITION: U8.8; also elsewhere on the board
/Common Control/REFUND: U8.6; also elsewhere on the board
/Common Control/TEST_STATUS_N: U7.28 (PA6); also elsewhere on the board
/GPIO/PA0_L1_HOLD_CO: RN1.8 (R7), U7.22 (PA0EXTCLK), U8.1
/GPIO/PA1_L2_HOLD_CO: RN1.7 (R6), U7.23 (PA1), U8.13
/GPIO/PA2_L3_HOLD_CO: RN1.4 (R3), U7.24 (PA2), U9.3
/GPIO/PA3_L4_HOLD_CO: RN1.3 (R2), U7.25 (PA3), U9.13
/GPIO/PA7: D16.1 (K), U7.1 (PA7)
/GPIO/PC0_L1_COIN_CONTROL: RN1.9 (R8), U7.2 (PC0), U8.11
/GPIO/PC1_L2_COIN_CONTROL: RN1.6 (R5), U7.3 (PC1), U9.5
/GPIO/PC2_L3_COIN_CONTROL: RN1.5 (R4), U7.4 (PC2), U9.11
/GPIO/PC3_L4_COIN_CONTROL: RN1.2 (R1), U7.5 (PC3), U9.1
/GPIO/PF0_REFUND: R7.1, RN1.11 (R10), U7.16 (PF0XTAL32K1), U8.5
/GPIO/PF1_DISPOSITION: RN1.10 (R9), U7.17 (PF1XTAL32K2), U8.9
/GPIO/RS232_RXD: JP3.1 (A); also elsewhere on the board
/GPIO/RS232_TXD: JP2.1 (A); also elsewhere on the board
/GPIO/TTL_RXD: J5.3, J7.4, JP3.3 (B)
/GPIO/TTL_TXD: J5.2, J7.5, JP2.3 (B)
/GPIO/UART_RXD: JP3.2 (C), U7.27 (PA5)
/GPIO/UART_TXD: JP2.2 (C), U7.26 (PA4)
/GPIO/UPDI: J7.2, JP1.2 (B), U7.19 (UPDI)
/GPIO/UPDI_EXT: J5.5, JP1.1 (A)
/GPIO/~RESET: C13.1, R8.2, SW1.1, U7.18 (PF6*RESET)
GND: C11.2, C12.2, C13.2, C14.2, C15.2, C16.2, C19.2, J5.6, J7.1, R7.2, RN1.1 (common), SW1.2, U7.15 (GND), U7.21 (GND), U8.3, U8.7 (GND), U9.7 (GND), U9.9; also elsewhere on the board
unnamed: D16.2 (A), R22.1

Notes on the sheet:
UPDI USB Serial 2v00 Rocket Scream
Serial Port Selection RS-232: JP1, JP2: 1-2 5V TTL: JP1, JP2: 2-3
1D Coin Controller
(c) 2020-2024, Howard M. Harte - WZ2Q https://github.com/hharte/1dcoinctrl
FTDI 5V USB UART
Pull-Downs for MCU, so relays are not activated during reset: If 10-resistor SIP is hard to source, use a common 9-resistor SIP and populate R26.

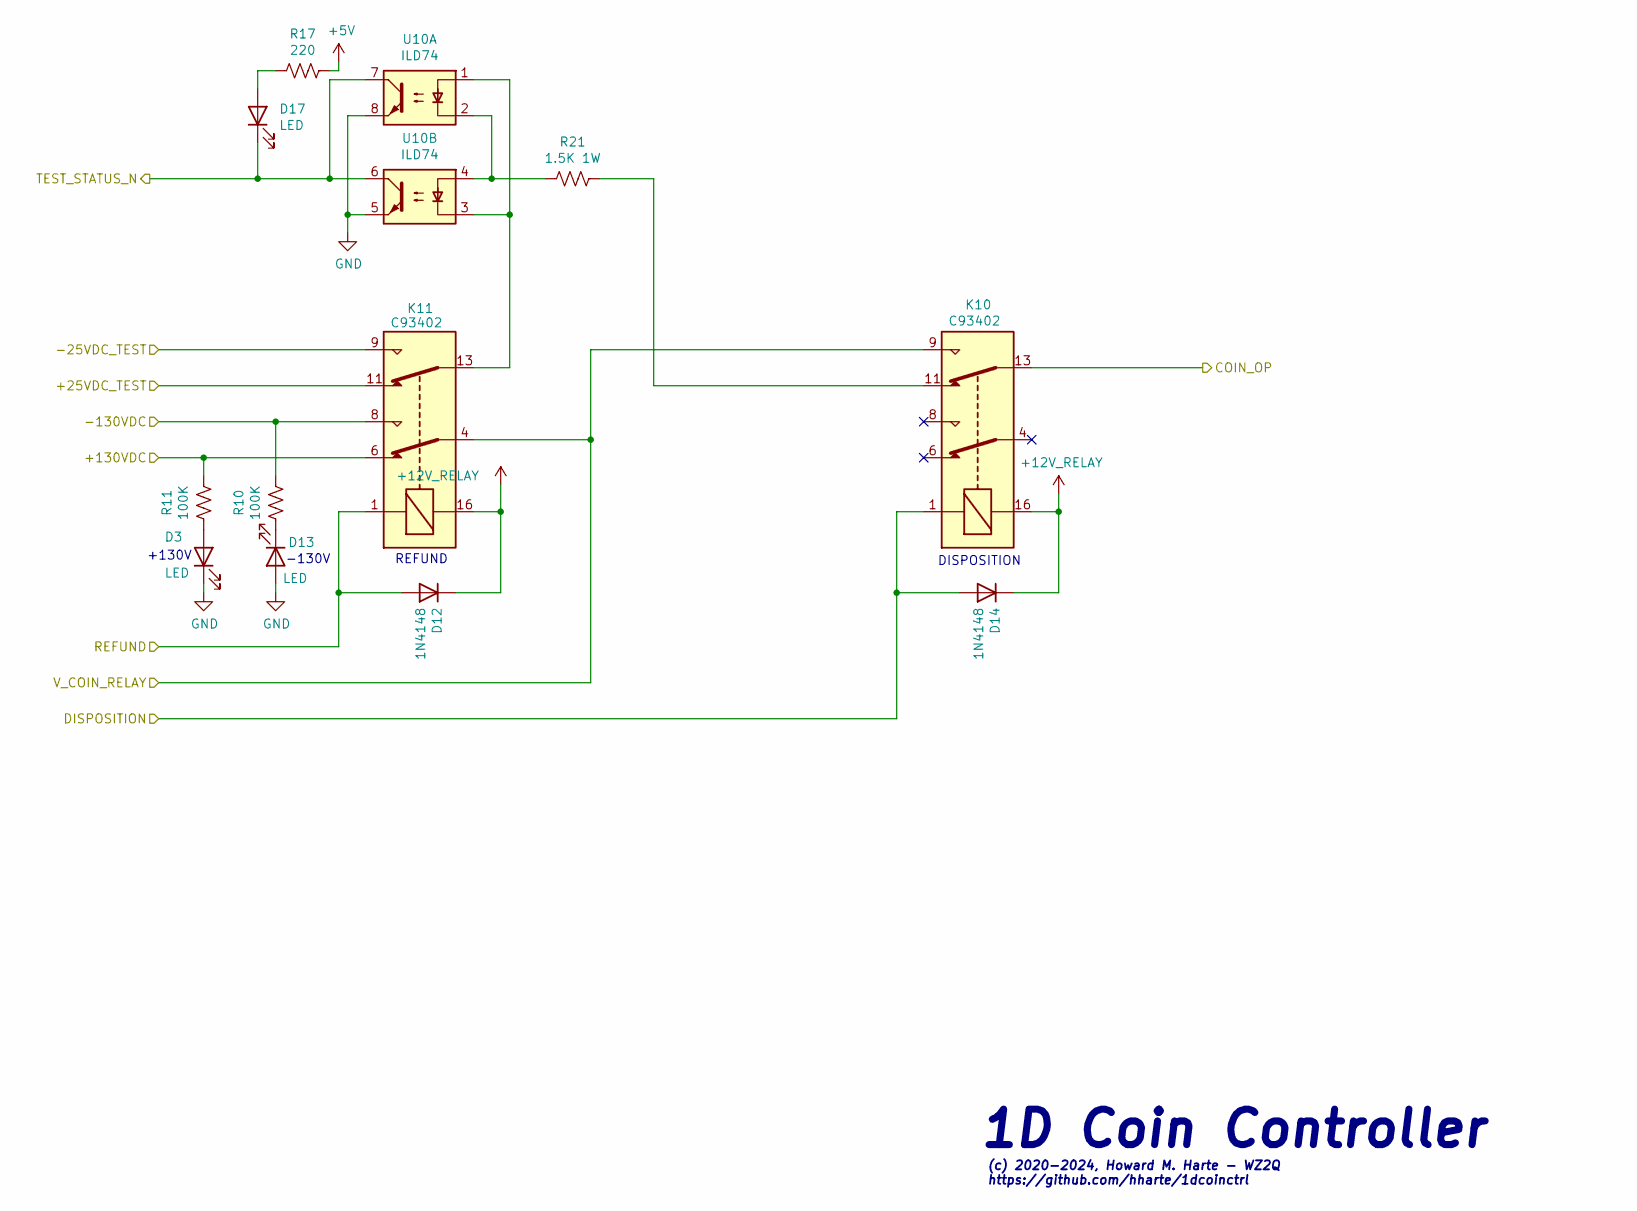
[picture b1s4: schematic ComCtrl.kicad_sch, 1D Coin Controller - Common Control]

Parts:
D3, D13, D17: LED; LED_D5.0mm; MPN XLUR12D; Digi-Key_PN 1497-1031-ND
D12, D14: 1N4148; D_DO-35_SOD27_P7.62mm_Horizontal; MPN 1N4148TA; Digi-Key_PN 1N4148TACT-ND
K10, K11: C93402; Relay_DPDT_Omron_G5V-2; MPN C93402; Digi-Key_PN PB1125-ND
R10, R11: 100K; R_Axial_DIN0207_L6.3mm_D2.5mm_P7.62mm_Horizontal; MPN CFM12JT100K; Digi-Key_PN S100KHCT-ND
R17: 220; R_Axial_DIN0207_L6.3mm_D2.5mm_P7.62mm_Horizontal; MPN CFM12JT220R; Digi-Key_PN S220HCT-ND
R21: 1.5K 1W; R_Axial_DIN0207_L6.3mm_D2.5mm_P10.16mm_Horizontal; MPN PR01000101501JR500; Digi-Key_PN PPC1.5KW-1CT-ND
U10: ILD74; DIP-8_W7.62mm_Socket; MPN CNY74-2H; Digi-Key_PN CNY74-2H-ND

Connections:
+5V: R17.1; also elsewhere on the board
+12V_RELAY: D12.1 (K), D14.1 (K), K10.16, K11.16; also elsewhere on the board
/Coin Line Control/COIN_OP: K10.13; also elsewhere on the board
/Common Control/+130VDC: K11.6, R11.1; also elsewhere on the board
/Common Control/-130VDC: K11.8, R10.1; also elsewhere on the board
/Common Control/DISPOSITION: D14.2 (A), K10.1; also elsewhere on the board
/Common Control/REFUND: D12.2 (A), K11.1; also elsewhere on the board
/Common Control/TEST_STATUS_N: D17.1 (K), U10.6, U10.7; also elsewhere on the board
/Common Control/V_COIN_RELAY: K10.9, K11.4; also elsewhere on the board
/Power/+25VDC: K11.11; also elsewhere on the board
/Power/-25VDC: K11.9; also elsewhere on the board
GND: D3.1 (K), D13.2 (A), U10.5, U10.8; also elsewhere on the board
unnamed: D3.2 (A), R11.2
unnamed: D13.1 (K), R10.2
unnamed: D17.2 (A), R17.2
unnamed: K10.11, R21.1
unnamed: K11.13, U10.1, U10.3
unnamed: R21.2, U10.2, U10.4

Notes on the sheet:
1D Coin Controller
DISPOSITION
+130V
REFUND
(c) 2020-2024, Howard M. Harte - WZ2Q https://github.com/hharte/1dcoinctrl
-130V

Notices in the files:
firmware/1DCOINCTRL.X/mcc_generated_files/pin_manager.h:
(c) 2018 Microchip Technology Inc. and its subsidiaries.
firmware/1dcoinctrl/1dcoinctrl.ino:
MIT License
Copyright (c) 2024 Howard M. Harte
hardware/1d_coinctrl.kicad_pcb:
4-Line Coin Controller Iss 4 (c) 2020-2024 Howard M. Harte - WZ2Q
hardware/1d_coinctrl_r2.kicad_pcb:
(c) 2020-2022 Howard M. Harte - WZ2Q
